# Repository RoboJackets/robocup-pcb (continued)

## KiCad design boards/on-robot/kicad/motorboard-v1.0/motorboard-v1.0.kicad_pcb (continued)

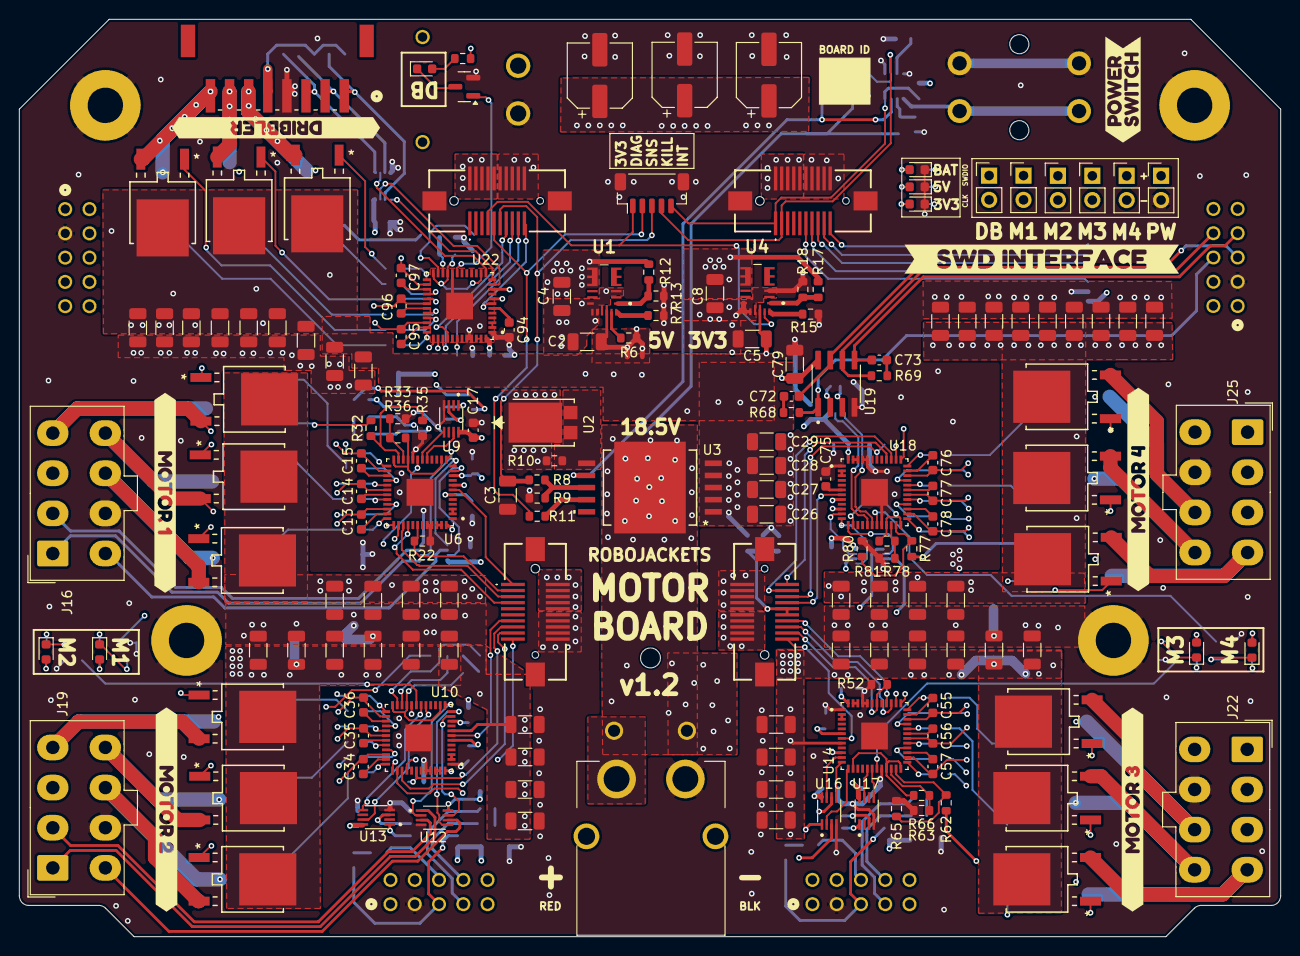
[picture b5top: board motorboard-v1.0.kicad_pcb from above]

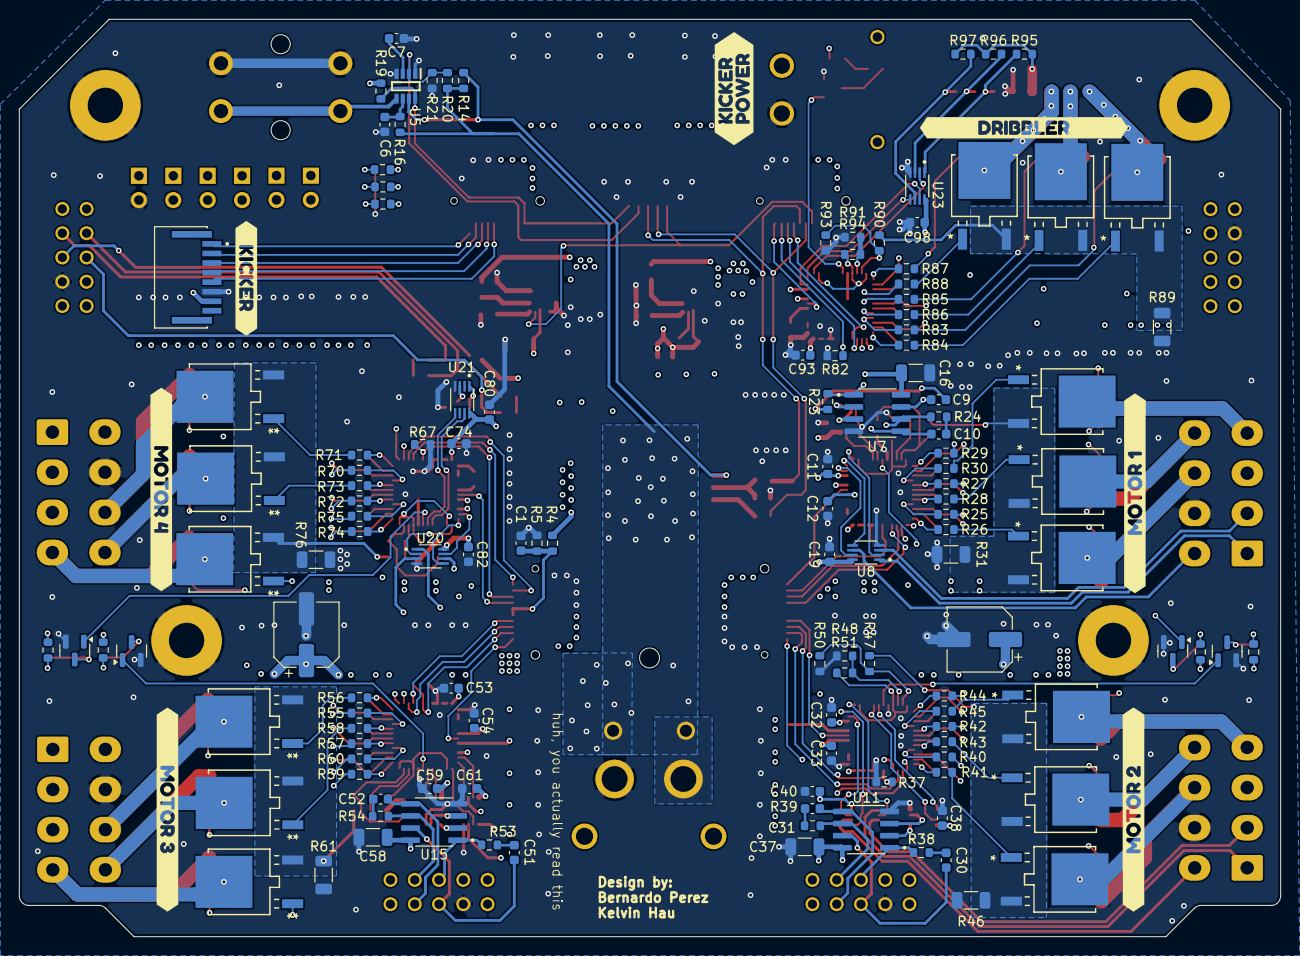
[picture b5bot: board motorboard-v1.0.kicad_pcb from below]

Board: 4 copper layers, 132.0 x 96.0 mm, 315 parts (135 on the bottom side), 272 nets.

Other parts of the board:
kibuzzard-679DAD2E: G***; kibuzzard-679DAD2E
kibuzzard-679DAD96, kibuzzard-679DAD96#2: G***; kibuzzard-679DAD96
kibuzzard-679DB05F, kibuzzard-679DB05F#2: G***; kibuzzard-679DB05F
kibuzzard-679DB7F8: G***; kibuzzard-679DB7F8
kibuzzard-679DB9B8: G***; kibuzzard-679DB9B8
kibuzzard-679DB034, kibuzzard-679DB034#2: G***; kibuzzard-679DB034
kibuzzard-679DB049, kibuzzard-679DB049#2: G***; kibuzzard-679DB049
kibuzzard-679DB095, kibuzzard-679DB095#2: G***; kibuzzard-679DB095
kibuzzard-679DBA21: G***; kibuzzard-679DBA21

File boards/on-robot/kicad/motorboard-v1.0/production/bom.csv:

Designator,Footprint,Quantity,Value,LCSC Part #
"C1, C11, C13, C14, C15, C17, C19, C32, C34, C35, C36, C38, C40, C53, C55, C56, C57, C59, C61, C74, C76, C77, C78, C80, C82, C93, C95, C96, C97, C98",0603,30,100nF,
"C10, C30, C31, C51, C52, C72, C73, C9",0603,8,0.1nF,
"C100, C101, C102, C104, C105, C106, C107, C108, C109, C18, C2, C20, C21, C22, C24, C25, C26, C27, C28, C29, C39, C41, C42, C43, C45, C46, C47, C48, C49, C5, C50, C60, C62, C63, C64, C66, C67, C68, C69, C70, C71, C81, C83, C84, C85, C87, C88, C89, C90, C91, C92, C99",1206,52,10uF,
"C103, C23, C44, C65, C86",CP_Elec_6.3x7.7,5,220uF,
"C12, C33, C54, C75, C94",0603,5,1uF,
"C16, C37, C58, C79",1206,4,10nF,
"C3, C4, C8",1206,3,22uF,
C6,0603,1,10nF,
C7,1206,1,470nF,
"D1, D2, D3, D4, D5, D6, D7, D8",0603,8,GREEN,
"H1, H2, H3, H4",MountingHole_3.7mm_Pad,4,MountingHole_Pad,
J11,JST_SH_BM05B-SRSS-TB_1x05-1MP_P1.00mm_Vertical,1,JST_01x05,
J12,XT30PWM,1,XT30PW-M,
"J13, J18, J21, J24, J27, J29",PinHeader_1x02_P2.54mm_Vertical,6,Conn_01x02,
J14,AMPHENOL_HFW8R-1STE1H1LF,1,HFW8R-1STE1H1LF,
J15,XT60PWM,1,XT60PW-M,
"J16, J19, J22, J25",CON_39306088,4,39301080,
"J17, J20, J23, J26",CONN_6002RB_3MM,4,N2510-6002RB,
J28,CONN_S8B-PH-SM4-TB_JST,1,S8B-PH-SM4-TB,
"J4, J5, J8, J9",529010274,4,52901-0274,
"Q1, Q10, Q11, Q12, Q13, Q15, Q16, Q17, Q18, Q19, Q2, Q20, Q22, Q23, Q24, Q25, Q26, Q27, Q29, Q3, Q30, Q31, Q32, Q33, Q34, Q4, Q5, Q6, Q8, Q9",DPAKTO-252_A2_STM,30,STD140N6F7,
"Q14, Q21, Q28, Q35, Q7",SOT-23,5,BSS123,
"R1, R35, R36, R50, R51, R65, R66, R80, R81",0603,9,5.6k,
"R10, R16, R19, R2, R3, R32, R33, R34, R47, R48, R49, R62, R63, R64, R77, R78, R79, R90, R91, R92",0603,20,1k,
"R11, R14, R22, R37, R5, R52, R67, R8, R82",0603,9,10k,
"R12, R17, R6",0603,3,160k,
R13,0603,1,30.1k,
R15,0603,1,29.4k,
R18,0603,1,51k,
R20,0603,1,583k,
R21,0603,1,100k,
"R23, R24, R38, R39, R53, R54, R68, R69",0603,8,120,
"R25, R26, R27, R28, R29, R30, R40, R41, R42, R43, R44, R45, R55, R56, R57, R58, R59, R60, R70, R71, R72, R73, R74, R75, R83, R84, R85, R86, R87, R88",0603,30,62,
"R31, R46, R61, R76, R89",1206,5,10m,
R4,0603,1,68k,
R7,0603,1,43.2k,
R9,0603,1,3k,
"R93, R94",0603,2,7.5k,
"R95, R96, R97",0603,3,R,
SW1,B3J-1000,1,B3J-1100,
"U1, U4",MPM3620GQVP,2,MPM3620GQV-P,
"U10, U14, U18, U22, U6",IC_STSPIN32F0A,5,STSPIN32F0A,
"U11, U15, U19, U7",SOIC127P599X175-8N,4,SN75157DR,
"U12, U13, U16, U17, U20, U21, U23, U8, U9",SOP50P310X90-8N,9,SN74LVC3G17DCUR,
U2,DIO_10100V_ONS,1,FSV10100V,
U3,SO_E006ASP-E_STM,1,VN5E006ASPTR-E,
U5,SOT65P280X100-8N,1,LTC2955-1,
X1,FUSE_01530007Z,1,01530007Z,
